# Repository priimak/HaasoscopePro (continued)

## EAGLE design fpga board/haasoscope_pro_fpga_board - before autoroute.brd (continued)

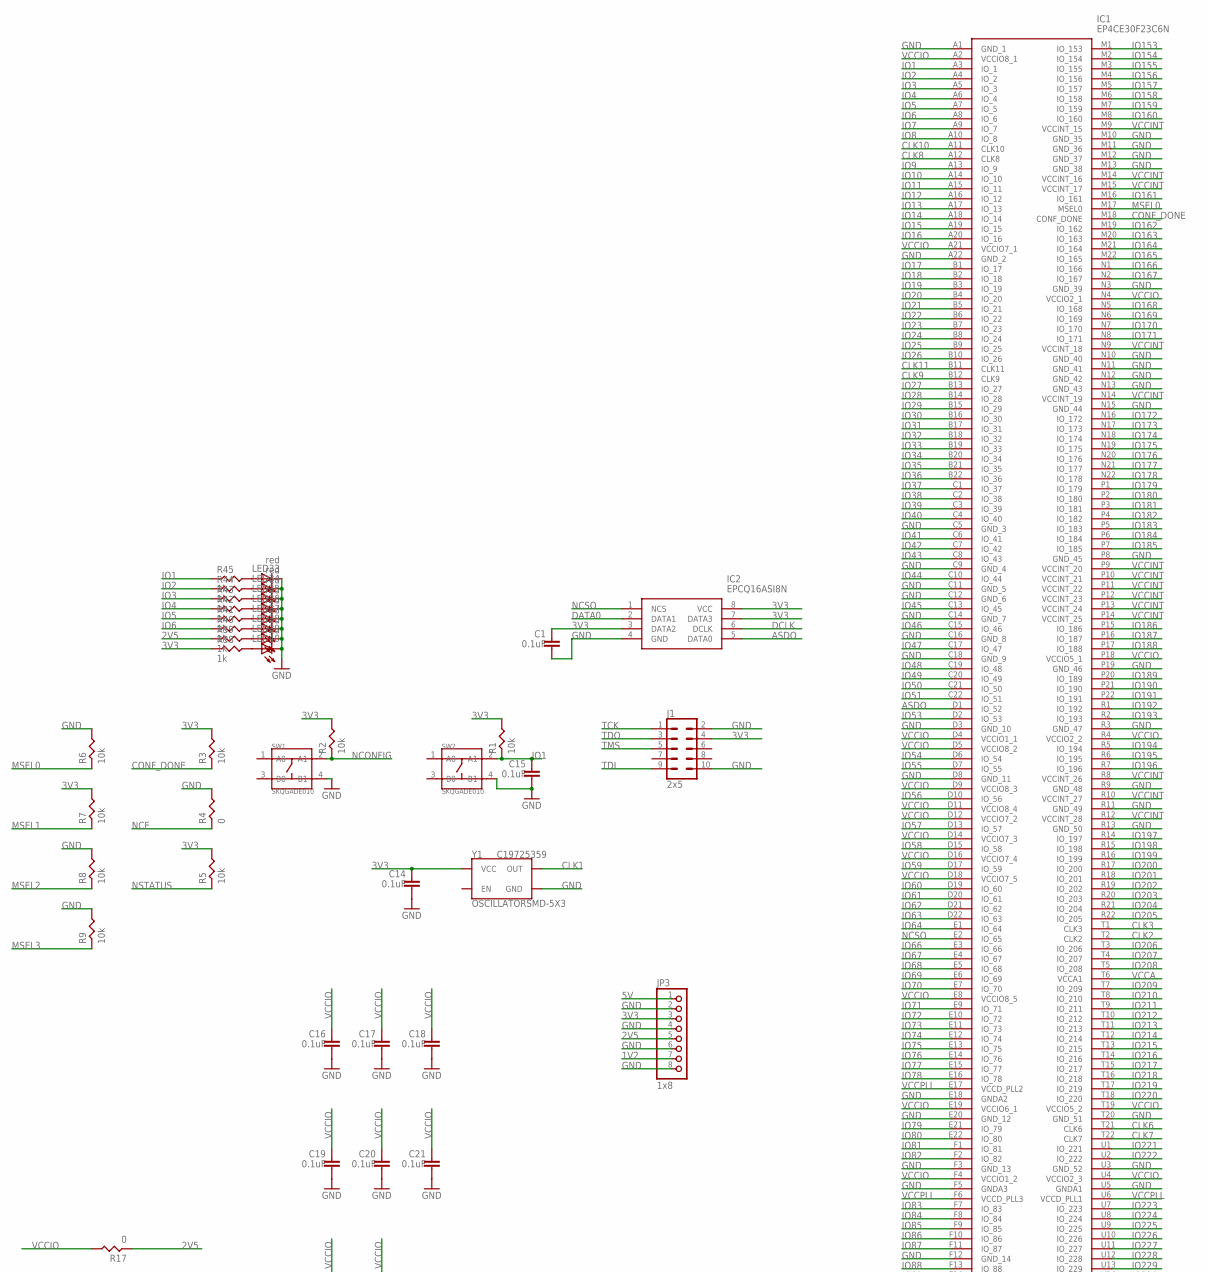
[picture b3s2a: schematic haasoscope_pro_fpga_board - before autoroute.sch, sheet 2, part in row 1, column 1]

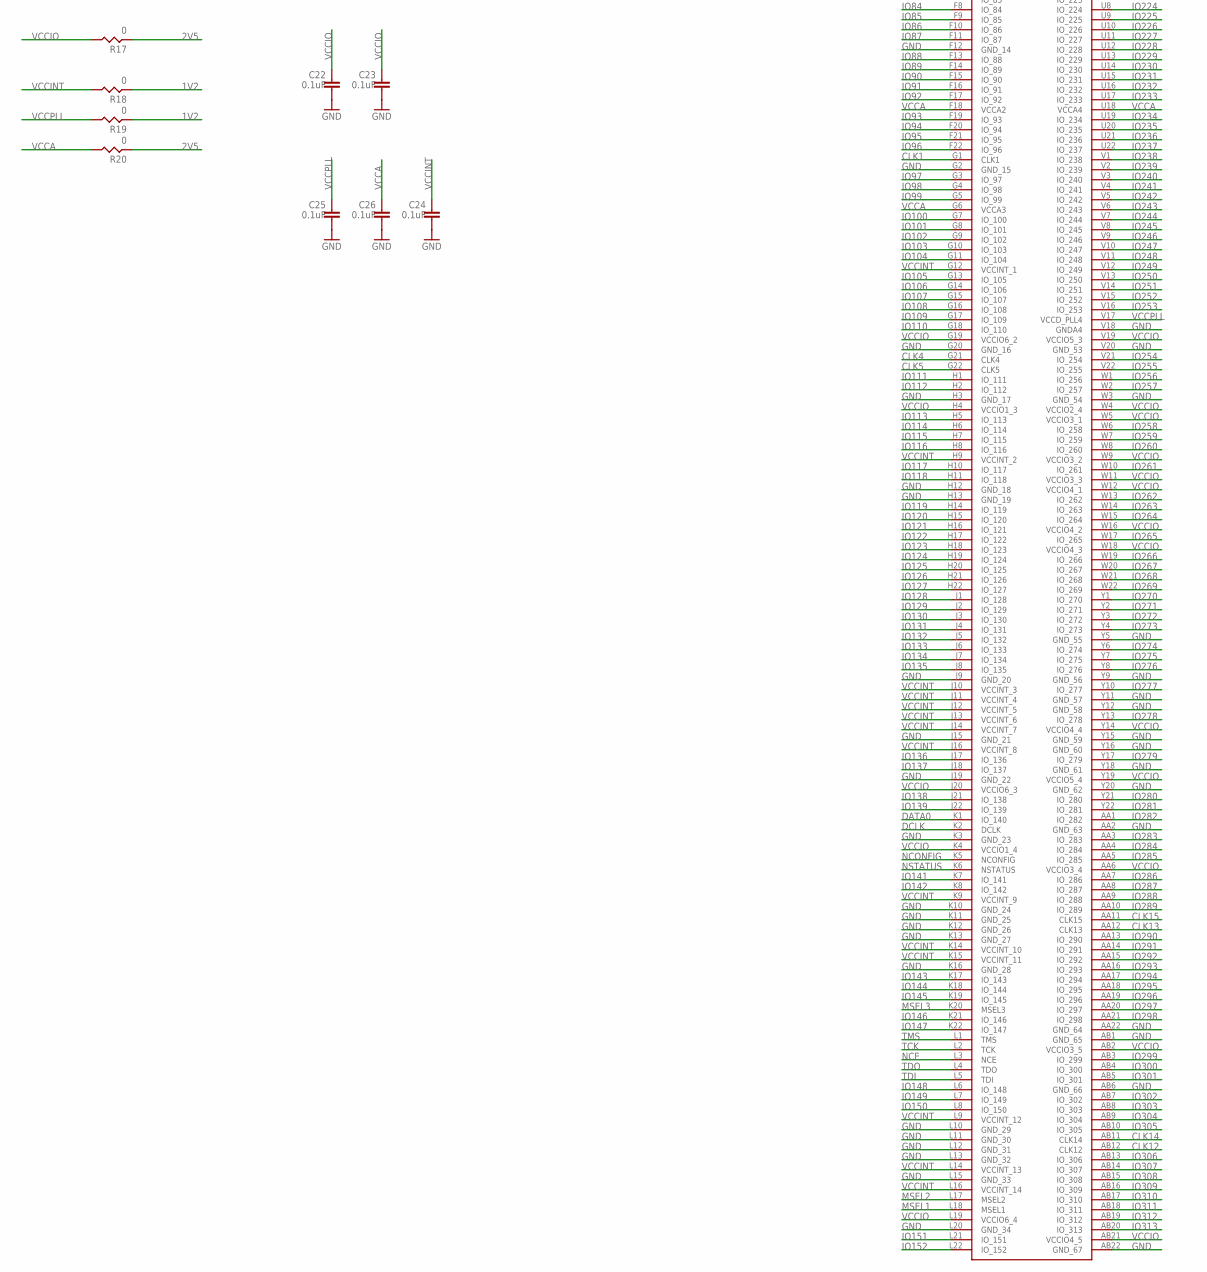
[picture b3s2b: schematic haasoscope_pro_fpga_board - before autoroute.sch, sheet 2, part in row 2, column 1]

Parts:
C1, C14, C15, C16, C17, C18, C19, C20, C21, C22, C23, C24, C25, C26: 0.1uF; RESC0402_N
IC1: EP4CE30F23C6N; BGA484C100P22X22_2300X2300X240
IC2: EPCQ16ASI8N; SOIC127P600X175-8N
J1: 2x5; 2X5-SHROUDED
JP3: 1x8; 1X08
LED33, LED34, LED35, LED36, LED37, LED38, LED39, LED40: red; CHIP-LED0603
R1, R2, R3, R5, R6, R7, R8, R9: 10k; RES-0402
R4, R17, R18, R19, R20: 0; RES-0402
R38, R39, R40, R41, R42, R43, R44, R45: 1k; RES-0402
SW1, SW2: SKQGADE010; SW4-SMD-5.2X5.2X1.5MM
Y1: OSCILLATORSMD-5X3; OSCILLATOR-SMD-5X3.2; LCSC C19725359

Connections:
1V2: JP3.7, R18.P$1, R19.P$1; also elsewhere on the board
2V5: JP3.5, R17.P$1, R20.P$1, R39.P$1; also elsewhere on the board
3V3: C1.2, C14.2, IC2.3 (DATA2), IC2.7 (DATA3), IC2.8 (VCC), J1.4, JP3.3, R1.P$2, R2.P$2, R3.P$2, R5.P$2, R7.P$2, R38.P$1, Y1.4 (VCC); also elsewhere on the board
5V: JP3.1; also elsewhere on the board
ASDO: IC1.D1 (IO_52), IC2.5 (DATA0); also elsewhere on the board
CLK1: IC1.G1 (CLK1), Y1.3 (OUT); also elsewhere on the board
CLK2: IC1.T2 (CLK2); also elsewhere on the board
CLK3: IC1.T1 (CLK3); also elsewhere on the board
CLK4: IC1.G21 (CLK4); also elsewhere on the board
CLK5: IC1.G22 (CLK5); also elsewhere on the board
CLK6: IC1.T21 (CLK6); also elsewhere on the board
CLK7: IC1.T22 (CLK7); also elsewhere on the board
CLK8: IC1.A12 (CLK8); also elsewhere on the board
CLK9: IC1.B12 (CLK9); also elsewhere on the board
CLK10: IC1.A11 (CLK10); also elsewhere on the board
CLK11: IC1.B11 (CLK11); also elsewhere on the board
CLK12: IC1.AB12 (CLK12); also elsewhere on the board
CLK13: IC1.AA12 (CLK13); also elsewhere on the board
CLK14: IC1.AB11 (CLK14); also elsewhere on the board
CLK15: IC1.AA11 (CLK15); also elsewhere on the board
CONF_DONE: IC1.M18 (CONF_DONE), R3.P$1
DATA0: IC1.K1 (IO_140), IC2.2 (DATA1); also elsewhere on the board
DCLK: IC1.K2 (DCLK), IC2.6 (DCLK)
GND: C1.1, C14.1, C15.1, C16.1, C17.1, C18.1, C19.1, C20.1, C21.1, C22.1, C23.1, C24.1, C25.1, C26.1, IC1.A1 (GND_1), IC1.A22 (GND_2), IC1.AA2 (GND_63), IC1.AA22 (GND_64), IC1.AB1 (GND_65), IC1.AB6 (GND_66), IC1.AB22 (GND_67), IC1.C5 (GND_3), IC1.C9 (GND_4), IC1.C11 (GND_5), IC1.C12 (GND_6), IC1.C14 (GND_7), IC1.C16 (GND_8), IC1.C18 (GND_9), IC1.D3 (GND_10), IC1.D8 (GND_11), IC1.E18 (GNDA2), IC1.E20 (GND_12), IC1.F3 (GND_13), IC1.F5 (GNDA3), IC1.F12 (GND_14), IC1.G2 (GND_15), IC1.G20 (GND_16), IC1.H3 (GND_17), IC1.H12 (GND_18), IC1.H13 (GND_19), IC1.J9 (GND_20), IC1.J15 (GND_21), IC1.J19 (GND_22), IC1.K3 (GND_23), IC1.K10 (GND_24), IC1.K11 (GND_25), IC1.K12 (GND_26), IC1.K13 (GND_27), IC1.K16 (GND_28), IC1.L10 (GND_29), IC1.L11 (GND_30), IC1.L12 (GND_31), IC1.L13 (GND_32), IC1.L15 (GND_33), IC1.L20 (GND_34), IC1.M10 (GND_35), IC1.M11 (GND_36), IC1.M12 (GND_37), IC1.M13 (GND_38), IC1.N3 (GND_39), IC1.N10 (GND_40), IC1.N11 (GND_41), IC1.N12 (GND_42), IC1.N13 (GND_43), IC1.N15 (GND_44), IC1.P8 (GND_45), IC1.P19 (GND_46), IC1.R3 (GND_47), IC1.R9 (GND_48), IC1.R11 (GND_49), IC1.R13 (GND_50), IC1.T20 (GND_51), IC1.U3 (GND_52), IC1.U5 (GNDA1), IC1.V18 (GNDA4), IC1.V20 (GND_53), IC1.W3 (GND_54), IC1.Y5 (GND_55), IC1.Y9 (GND_56), IC1.Y11 (GND_57), IC1.Y12 (GND_58), IC1.Y15 (GND_59), IC1.Y16 (GND_60), IC1.Y18 (GND_61), IC1.Y20 (GND_62), IC2.4 (GND), J1.2, J1.10, JP3.2, JP3.4, JP3.6, JP3.8, LED33.C, LED34.C, LED35.C, LED36.C, LED37.C, LED38.C, LED39.C, LED40.C, R4.P$2, R6.P$2, R8.P$2, R9.P$2, SW1.4 (B1), SW2.4 (B1), Y1.2 (GND); also elsewhere on the board
IO1: C15.2, IC1.A3 (IO_1), R1.P$1, R45.P$1, SW2.2 (A1); also elsewhere on the board
IO2: IC1.A4 (IO_2), R44.P$1; also elsewhere on the board
IO3: IC1.A5 (IO_3), R43.P$1; also elsewhere on the board
IO4: IC1.A6 (IO_4), R42.P$1; also elsewhere on the board
IO5: IC1.A7 (IO_5), R41.P$1; also elsewhere on the board
IO6: IC1.A8 (IO_6), R40.P$1; also elsewhere on the board
IO7: IC1.A9 (IO_7); also elsewhere on the board
IO8: IC1.A10 (IO_8); also elsewhere on the board
IO9: IC1.A13 (IO_9); also elsewhere on the board
IO10: IC1.A14 (IO_10); also elsewhere on the board
IO11: IC1.A15 (IO_11); also elsewhere on the board
IO12: IC1.A16 (IO_12); also elsewhere on the board
IO13: IC1.A17 (IO_13); also elsewhere on the board
IO14: IC1.A18 (IO_14); also elsewhere on the board
IO15: IC1.A19 (IO_15); also elsewhere on the board
IO16: IC1.A20 (IO_16); also elsewhere on the board
IO17: IC1.B1 (IO_17); also elsewhere on the board
IO18: IC1.B2 (IO_18); also elsewhere on the board
IO19: IC1.B3 (IO_19); also elsewhere on the board
IO20: IC1.B4 (IO_20); also elsewhere on the board
IO21: IC1.B5 (IO_21); also elsewhere on the board
IO22: IC1.B6 (IO_22); also elsewhere on the board
IO23: IC1.B7 (IO_23); also elsewhere on the board
IO24: IC1.B8 (IO_24); also elsewhere on the board
IO25: IC1.B9 (IO_25); also elsewhere on the board
IO26: IC1.B10 (IO_26); also elsewhere on the board
IO27: IC1.B13 (IO_27); also elsewhere on the board
IO28: IC1.B14 (IO_28); also elsewhere on the board
IO29: IC1.B15 (IO_29); also elsewhere on the board
IO30: IC1.B16 (IO_30); also elsewhere on the board
IO31: IC1.B17 (IO_31); also elsewhere on the board
IO32: IC1.B18 (IO_32); also elsewhere on the board
IO33: IC1.B19 (IO_33); also elsewhere on the board
IO34: IC1.B20 (IO_34); also elsewhere on the board
IO35: IC1.B21 (IO_35); also elsewhere on the board
IO36: IC1.B22 (IO_36); also elsewhere on the board
IO37: IC1.C1 (IO_37); also elsewhere on the board
IO38: IC1.C2 (IO_38); also elsewhere on the board
IO39: IC1.C3 (IO_39); also elsewhere on the board
IO40: IC1.C4 (IO_40); also elsewhere on the board
IO41: IC1.C6 (IO_41); also elsewhere on the board
IO42: IC1.C7 (IO_42); also elsewhere on the board
IO43: IC1.C8 (IO_43); also elsewhere on the board
IO44: IC1.C10 (IO_44); also elsewhere on the board
IO45: IC1.C13 (IO_45); also elsewhere on the board
IO46: IC1.C15 (IO_46); also elsewhere on the board
IO47: IC1.C17 (IO_47); also elsewhere on the board
IO48: IC1.C19 (IO_48); also elsewhere on the board
IO49: IC1.C20 (IO_49); also elsewhere on the board
IO50: IC1.C21 (IO_50); also elsewhere on the board
IO51: IC1.C22 (IO_51); also elsewhere on the board
IO53: IC1.D2 (IO_53); also elsewhere on the board
IO54: IC1.D6 (IO_54); also elsewhere on the board
IO55: IC1.D7 (IO_55); also elsewhere on the board
IO56: IC1.D10 (IO_56); also elsewhere on the board
IO57: IC1.D13 (IO_57); also elsewhere on the board
IO58: IC1.D15 (IO_58); also elsewhere on the board
IO59: IC1.D17 (IO_59); also elsewhere on the board
IO60: IC1.D19 (IO_60); also elsewhere on the board
IO61: IC1.D20 (IO_61); also elsewhere on the board
IO62: IC1.D21 (IO_62); also elsewhere on the board
IO63: IC1.D22 (IO_63); also elsewhere on the board
IO64: IC1.E1 (IO_64); also elsewhere on the board
IO66: IC1.E3 (IO_66); also elsewhere on the board
IO67: IC1.E4 (IO_67); also elsewhere on the board
IO68: IC1.E5 (IO_68); also elsewhere on the board
IO69: IC1.E6 (IO_69); also elsewhere on the board
IO70: IC1.E7 (IO_70); also elsewhere on the board
IO71: IC1.E9 (IO_71); also elsewhere on the board
IO72: IC1.E10 (IO_72); also elsewhere on the board
IO73: IC1.E11 (IO_73); also elsewhere on the board
IO74: IC1.E12 (IO_74); also elsewhere on the board
IO75: IC1.E13 (IO_75); also elsewhere on the board
IO76: IC1.E14 (IO_76); also elsewhere on the board
IO77: IC1.E15 (IO_77); also elsewhere on the board
IO78: IC1.E16 (IO_78); also elsewhere on the board
IO79: IC1.E21 (IO_79); also elsewhere on the board
IO80: IC1.E22 (IO_80); also elsewhere on the board
IO81: IC1.F1 (IO_81); also elsewhere on the board
IO82: IC1.F2 (IO_82); also elsewhere on the board
IO83: IC1.F7 (IO_83); also elsewhere on the board
IO84: IC1.F8 (IO_84); also elsewhere on the board
IO85: IC1.F9 (IO_85); also elsewhere on the board
IO86: IC1.F10 (IO_86); also elsewhere on the board
IO87: IC1.F11 (IO_87); also elsewhere on the board
IO88: IC1.F13 (IO_88); also elsewhere on the board
IO89: IC1.F14 (IO_89); also elsewhere on the board
IO90: IC1.F15 (IO_90); also elsewhere on the board
IO91: IC1.F16 (IO_91); also elsewhere on the board
IO92: IC1.F17 (IO_92); also elsewhere on the board
IO93: IC1.F19 (IO_93); also elsewhere on the board
IO94: IC1.F20 (IO_94); also elsewhere on the board
IO95: IC1.F21 (IO_95); also elsewhere on the board
IO96: IC1.F22 (IO_96); also elsewhere on the board
IO97: IC1.G3 (IO_97); also elsewhere on the board
IO98: IC1.G4 (IO_98); also elsewhere on the board
IO99: IC1.G5 (IO_99); also elsewhere on the board
IO100: IC1.G7 (IO_100); also elsewhere on the board
IO101: IC1.G8 (IO_101); also elsewhere on the board
IO102: IC1.G9 (IO_102); also elsewhere on the board
IO103: IC1.G10 (IO_103); also elsewhere on the board
IO104: IC1.G11 (IO_104); also elsewhere on the board
IO105: IC1.G13 (IO_105); also elsewhere on the board
IO106: IC1.G14 (IO_106); also elsewhere on the board
IO107: IC1.G15 (IO_107); also elsewhere on the board
IO108: IC1.G16 (IO_108); also elsewhere on the board
IO109: IC1.G17 (IO_109); also elsewhere on the board
IO110: IC1.G18 (IO_110); also elsewhere on the board
IO111: IC1.H1 (IO_111); also elsewhere on the board
IO112: IC1.H2 (IO_112); also elsewhere on the board
IO113: IC1.H5 (IO_113); also elsewhere on the board
IO114: IC1.H6 (IO_114); also elsewhere on the board
IO115: IC1.H7 (IO_115); also elsewhere on the board
IO116: IC1.H8 (IO_116); also elsewhere on the board
IO117: IC1.H10 (IO_117); also elsewhere on the board
IO118: IC1.H11 (IO_118); also elsewhere on the board
IO119: IC1.H14 (IO_119); also elsewhere on the board
IO120: IC1.H15 (IO_120); also elsewhere on the board
IO121: IC1.H16 (IO_121); also elsewhere on the board
IO122: IC1.H17 (IO_122); also elsewhere on the board
IO123: IC1.H18 (IO_123); also elsewhere on the board
IO124: IC1.H19 (IO_124); also elsewhere on the board
IO125: IC1.H20 (IO_125); also elsewhere on the board
IO126: IC1.H21 (IO_126); also elsewhere on the board
IO127: IC1.H22 (IO_127); also elsewhere on the board
IO128: IC1.J1 (IO_128); also elsewhere on the board
IO129: IC1.J2 (IO_129); also elsewhere on the board
IO130: IC1.J3 (IO_130); also elsewhere on the board
IO131: IC1.J4 (IO_131); also elsewhere on the board
IO132: IC1.J5 (IO_132); also elsewhere on the board
IO133: IC1.J6 (IO_133); also elsewhere on the board
IO134: IC1.J7 (IO_134); also elsewhere on the board
IO135: IC1.J8 (IO_135); also elsewhere on the board
IO136: IC1.J17 (IO_136); also elsewhere on the board
IO137: IC1.J18 (IO_137); also elsewhere on the board
IO138: IC1.J21 (IO_138); also elsewhere on the board
IO139: IC1.J22 (IO_139); also elsewhere on the board
IO141: IC1.K7 (IO_141); also elsewhere on the board
IO142: IC1.K8 (IO_142); also elsewhere on the board
IO143: IC1.K17 (IO_143); also elsewhere on the board
IO144: IC1.K18 (IO_144); also elsewhere on the board
IO145: IC1.K19 (IO_145); also elsewhere on the board
IO146: IC1.K21 (IO_146); also elsewhere on the board
IO147: IC1.K22 (IO_147); also elsewhere on the board
IO148: IC1.L6 (IO_148); also elsewhere on the board
IO149: IC1.L7 (IO_149); also elsewhere on the board
IO150: IC1.L8 (IO_150); also elsewhere on the board
IO151: IC1.L21 (IO_151); also elsewhere on the board
IO152: IC1.L22 (IO_152); also elsewhere on the board
IO153: IC1.M1 (IO_153); also elsewhere on the board
IO154: IC1.M2 (IO_154); also elsewhere on the board
IO155: IC1.M3 (IO_155); also elsewhere on the board
IO156: IC1.M4 (IO_156); also elsewhere on the board
IO157: IC1.M5 (IO_157); also elsewhere on the board
IO158: IC1.M6 (IO_158); also elsewhere on the board
IO159: IC1.M7 (IO_159); also elsewhere on the board
IO160: IC1.M8 (IO_160); also elsewhere on the board
IO161: IC1.M16 (IO_161); also elsewhere on the board
IO162: IC1.M19 (IO_162); also elsewhere on the board
IO163: IC1.M20 (IO_163); also elsewhere on the board
IO164: IC1.M21 (IO_164); also elsewhere on the board
IO165: IC1.M22 (IO_165); also elsewhere on the board
IO166: IC1.N1 (IO_166); also elsewhere on the board
IO167: IC1.N2 (IO_167); also elsewhere on the board
IO168: IC1.N5 (IO_168); also elsewhere on the board
IO169: IC1.N6 (IO_169); also elsewhere on the board
IO170: IC1.N7 (IO_170); also elsewhere on the board
IO171: IC1.N8 (IO_171); also elsewhere on the board
IO172: IC1.N16 (IO_172); also elsewhere on the board
IO173: IC1.N17 (IO_173); also elsewhere on the board
IO174: IC1.N18 (IO_174); also elsewhere on the board
IO175: IC1.N19 (IO_175); also elsewhere on the board
IO176: IC1.N20 (IO_176); also elsewhere on the board
IO177: IC1.N21 (IO_177); also elsewhere on the board
IO178: IC1.N22 (IO_178); also elsewhere on the board
IO179: IC1.P1 (IO_179); also elsewhere on the board
IO180: IC1.P2 (IO_180); also elsewhere on the board
IO181: IC1.P3 (IO_181); also elsewhere on the board
IO182: IC1.P4 (IO_182); also elsewhere on the board
IO183: IC1.P5 (IO_183); also elsewhere on the board
IO184: IC1.P6 (IO_184); also elsewhere on the board
IO185: IC1.P7 (IO_185); also elsewhere on the board
IO186: IC1.P15 (IO_186); also elsewhere on the board
IO187: IC1.P16 (IO_187); also elsewhere on the board
IO188: IC1.P17 (IO_188); also elsewhere on the board
IO189: IC1.P20 (IO_189); also elsewhere on the board
IO190: IC1.P21 (IO_190); also elsewhere on the board
IO191: IC1.P22 (IO_191); also elsewhere on the board
IO192: IC1.R1 (IO_192); also elsewhere on the board
IO193: IC1.R2 (IO_193); also elsewhere on the board
IO194: IC1.R5 (IO_194); also elsewhere on the board
IO195: IC1.R6 (IO_195); also elsewhere on the board
IO196: IC1.R7 (IO_196); also elsewhere on the board
IO197: IC1.R14 (IO_197); also elsewhere on the board
IO198: IC1.R15 (IO_198); also elsewhere on the board
IO199: IC1.R16 (IO_199); also elsewhere on the board
IO200: IC1.R17 (IO_200); also elsewhere on the board
IO201: IC1.R18 (IO_201); also elsewhere on the board
IO202: IC1.R19 (IO_202); also elsewhere on the board
IO203: IC1.R20 (IO_203); also elsewhere on the board
IO204: IC1.R21 (IO_204); also elsewhere on the board
IO205: IC1.R22 (IO_205); also elsewhere on the board
IO206: IC1.T3 (IO_206); also elsewhere on the board
IO207: IC1.T4 (IO_207); also elsewhere on the board
IO208: IC1.T5 (IO_208); also elsewhere on the board
IO209: IC1.T7 (IO_209); also elsewhere on the board
IO210: IC1.T8 (IO_210); also elsewhere on the board
IO211: IC1.T9 (IO_211); also elsewhere on the board
IO212: IC1.T10 (IO_212); also elsewhere on the board
IO213: IC1.T11 (IO_213); also elsewhere on the board
IO214: IC1.T12 (IO_214); also elsewhere on the board
IO215: IC1.T13 (IO_215); also elsewhere on the board
IO216: IC1.T14 (IO_216); also elsewhere on the board
IO217: IC1.T15 (IO_217); also elsewhere on the board
IO218: IC1.T16 (IO_218); also elsewhere on the board
IO219: IC1.T17 (IO_219); also elsewhere on the board
IO220: IC1.T18 (IO_220); also elsewhere on the board
IO221: IC1.U1 (IO_221); also elsewhere on the board
IO222: IC1.U2 (IO_222); also elsewhere on the board
IO223: IC1.U7 (IO_223); also elsewhere on the board
IO224: IC1.U8 (IO_224); also elsewhere on the board
IO225: IC1.U9 (IO_225); also elsewhere on the board
IO226: IC1.U10 (IO_226); also elsewhere on the board
IO227: IC1.U11 (IO_227); also elsewhere on the board
IO228: IC1.U12 (IO_228); also elsewhere on the board
IO229: IC1.U13 (IO_229); also elsewhere on the board
IO230: IC1.U14 (IO_230); also elsewhere on the board
IO231: IC1.U15 (IO_231); also elsewhere on the board
IO232: IC1.U16 (IO_232); also elsewhere on the board
IO233: IC1.U17 (IO_233); also elsewhere on the board
IO234: IC1.U19 (IO_234); also elsewhere on the board
IO235: IC1.U20 (IO_235); also elsewhere on the board
IO236: IC1.U21 (IO_236); also elsewhere on the board
IO237: IC1.U22 (IO_237); also elsewhere on the board
IO238: IC1.V1 (IO_238); also elsewhere on the board
IO239: IC1.V2 (IO_239); also elsewhere on the board
IO240: IC1.V3 (IO_240); also elsewhere on the board
IO241: IC1.V4 (IO_241); also elsewhere on the board
IO242: IC1.V5 (IO_242); also elsewhere on the board
IO243: IC1.V6 (IO_243); also elsewhere on the board
IO244: IC1.V7 (IO_244); also elsewhere on the board
IO245: IC1.V8 (IO_245); also elsewhere on the board
IO246: IC1.V9 (IO_246); also elsewhere on the board
IO247: IC1.V10 (IO_247); also elsewhere on the board
IO248: IC1.V11 (IO_248); also elsewhere on the board
IO249: IC1.V12 (IO_249); also elsewhere on the board
IO250: IC1.V13 (IO_250); also elsewhere on the board
IO251: IC1.V14 (IO_251); also elsewhere on the board
IO252: IC1.V15 (IO_252); also elsewhere on the board
IO253: IC1.V16 (IO_253); also elsewhere on the board
IO254: IC1.V21 (IO_254); also elsewhere on the board
IO255: IC1.V22 (IO_255); also elsewhere on the board
IO256: IC1.W1 (IO_256); also elsewhere on the board
IO257: IC1.W2 (IO_257); also elsewhere on the board
IO258: IC1.W6 (IO_258); also elsewhere on the board
IO259: IC1.W7 (IO_259); also elsewhere on the board
IO260: IC1.W8 (IO_260); also elsewhere on the board
IO261: IC1.W10 (IO_261); also elsewhere on the board
IO262: IC1.W13 (IO_262); also elsewhere on the board
IO263: IC1.W14 (IO_263); also elsewhere on the board
IO264: IC1.W15 (IO_264); also elsewhere on the board
IO265: IC1.W17 (IO_265); also elsewhere on the board
IO266: IC1.W19 (IO_266); also elsewhere on the board
IO267: IC1.W20 (IO_267); also elsewhere on the board
IO268: IC1.W21 (IO_268); also elsewhere on the board
IO269: IC1.W22 (IO_269); also elsewhere on the board
IO270: IC1.Y1 (IO_270); also elsewhere on the board
IO271: IC1.Y2 (IO_271); also elsewhere on the board
IO272: IC1.Y3 (IO_272); also elsewhere on the board
IO273: IC1.Y4 (IO_273); also elsewhere on the board
IO274: IC1.Y6 (IO_274); also elsewhere on the board
IO275: IC1.Y7 (IO_275); also elsewhere on the board
IO276: IC1.Y8 (IO_276); also elsewhere on the board
IO277: IC1.Y10 (IO_277); also elsewhere on the board
IO278: IC1.Y13 (IO_278); also elsewhere on the board
IO279: IC1.Y17 (IO_279); also elsewhere on the board
IO280: IC1.Y21 (IO_280); also elsewhere on the board
IO281: IC1.Y22 (IO_281); also elsewhere on the board
IO282: IC1.AA1 (IO_282); also elsewhere on the board
IO283: IC1.AA3 (IO_283); also elsewhere on the board
IO284: IC1.AA4 (IO_284); also elsewhere on the board
IO285: IC1.AA5 (IO_285); also elsewhere on the board
IO286: IC1.AA7 (IO_286); also elsewhere on the board
IO287: IC1.AA8 (IO_287); also elsewhere on the board
IO288: IC1.AA9 (IO_288); also elsewhere on the board
IO289: IC1.AA10 (IO_289); also elsewhere on the board
IO290: IC1.AA13 (IO_290); also elsewhere on the board
IO291: IC1.AA14 (IO_291); also elsewhere on the board
IO292: IC1.AA15 (IO_292); also elsewhere on the board
IO293: IC1.AA16 (IO_293); also elsewhere on the board
IO294: IC1.AA17 (IO_294); also elsewhere on the board
IO295: IC1.AA18 (IO_295); also elsewhere on the board
IO296: IC1.AA19 (IO_296); also elsewhere on the board
IO297: IC1.AA20 (IO_297); also elsewhere on the board
IO298: IC1.AA21 (IO_298); also elsewhere on the board
IO299: IC1.AB3 (IO_299); also elsewhere on the board
IO300: IC1.AB4 (IO_300); also elsewhere on the board
IO301: IC1.AB5 (IO_301); also elsewhere on the board
IO302: IC1.AB7 (IO_302); also elsewhere on the board
IO303: IC1.AB8 (IO_303); also elsewhere on the board
IO304: IC1.AB9 (IO_304); also elsewhere on the board
IO305: IC1.AB10 (IO_305); also elsewhere on the board
IO306: IC1.AB13 (IO_306); also elsewhere on the board
IO307: IC1.AB14 (IO_307); also elsewhere on the board
IO308: IC1.AB15 (IO_308); also elsewhere on the board
IO309: IC1.AB16 (IO_309); also elsewhere on the board
IO310: IC1.AB17 (IO_310); also elsewhere on the board
IO311: IC1.AB18 (IO_311); also elsewhere on the board
IO312: IC1.AB19 (IO_312); also elsewhere on the board
IO313: IC1.AB20 (IO_313); also elsewhere on the board
MSEL0: IC1.M17 (MSEL0), R6.P$1
MSEL1: IC1.L18 (MSEL1), R7.P$1
MSEL2: IC1.L17 (MSEL2), R8.P$1
MSEL3: IC1.K20 (MSEL3), R9.P$1
unnamed: LED33.A, R45.P$2
unnamed: LED34.A, R44.P$2
unnamed: LED35.A, R43.P$2
unnamed: LED36.A, R42.P$2
unnamed: LED37.A, R41.P$2
unnamed: LED38.A, R40.P$2
unnamed: LED39.A, R39.P$2
unnamed: LED40.A, R38.P$2
NCE: IC1.L3 (NCE), R4.P$1
NCONFIG: IC1.K5 (NCONFIG), R2.P$1, SW1.2 (A1)
NCSO: IC1.E2 (IO_65), IC2.1 (NCS); also elsewhere on the board
NSTATUS: IC1.K6 (NSTATUS), R5.P$1
TCK: IC1.L2 (TCK), J1.1
TDI: IC1.L5 (TDI), J1.9
TDO: IC1.L4 (TDO), J1.3
TMS: IC1.L1 (TMS), J1.5
VCCA: C26.2, IC1.F18 (VCCA2), IC1.G6 (VCCA3), IC1.T6 (VCCA1), IC1.U18 (VCCA4), R20.P$2
VCCINT: C24.2, IC1.G12 (VCCINT_1), IC1.H9 (VCCINT_2), IC1.J10 (VCCINT_3), IC1.J11 (VCCINT_4), IC1.J12 (VCCINT_5), IC1.J13 (VCCINT_6), IC1.J14 (VCCINT_7), IC1.J16 (VCCINT_8), IC1.K9 (VCCINT_9), IC1.K14 (VCCINT_10), IC1.K15 (VCCINT_11), IC1.L9 (VCCINT_12), IC1.L14 (VCCINT_13), IC1.L16 (VCCINT_14), IC1.M9 (VCCINT_15), IC1.M14 (VCCINT_16), IC1.M15 (VCCINT_17), IC1.N9 (VCCINT_18), IC1.N14 (VCCINT_19), IC1.P9 (VCCINT_20), IC1.P10 (VCCINT_21), IC1.P11 (VCCINT_22), IC1.P12 (VCCINT_23), IC1.P13 (VCCINT_24), IC1.P14 (VCCINT_25), IC1.R8 (VCCINT_26), IC1.R10 (VCCINT_27), IC1.R12 (VCCINT_28), R18.P$2
VCCIO: C16.2, C17.2, C18.2, C19.2, C20.2, C21.2, C22.2, C23.2, IC1.A2 (VCCIO8_1), IC1.A21 (VCCIO7_1), IC1.AA6 (VCCIO3_4), IC1.AB2 (VCCIO3_5), IC1.AB21 (VCCIO4_5), IC1.D4 (VCCIO1_1), IC1.D5 (VCCIO8_2), IC1.D9 (VCCIO8_3), IC1.D11 (VCCIO8_4), IC1.D12 (VCCIO7_2), IC1.D14 (VCCIO7_3), IC1.D16 (VCCIO7_4), IC1.D18 (VCCIO7_5), IC1.E8 (VCCIO8_5), IC1.E19 (VCCIO6_1), IC1.F4 (VCCIO1_2), IC1.G19 (VCCIO6_2), IC1.H4 (VCCIO1_3), IC1.J20 (VCCIO6_3), IC1.K4 (VCCIO1_4), IC1.L19 (VCCIO6_4), IC1.N4 (VCCIO2_1), IC1.P18 (VCCIO5_1), IC1.R4 (VCCIO2_2), IC1.T19 (VCCIO5_2), IC1.U4 (VCCIO2_3), IC1.V19 (VCCIO5_3), IC1.W4 (VCCIO2_4), IC1.W5 (VCCIO3_1), IC1.W9 (VCCIO3_2), IC1.W11 (VCCIO3_3), IC1.W12 (VCCIO4_1), IC1.W16 (VCCIO4_2), IC1.W18 (VCCIO4_3), IC1.Y14 (VCCIO4_4), IC1.Y19 (VCCIO5_4), R17.P$2
VCCPLL: C25.2, IC1.E17 (VCCD_PLL2), IC1.F6 (VCCD_PLL3), IC1.U6 (VCCD_PLL1), IC1.V17 (VCCD_PLL4), R19.P$2

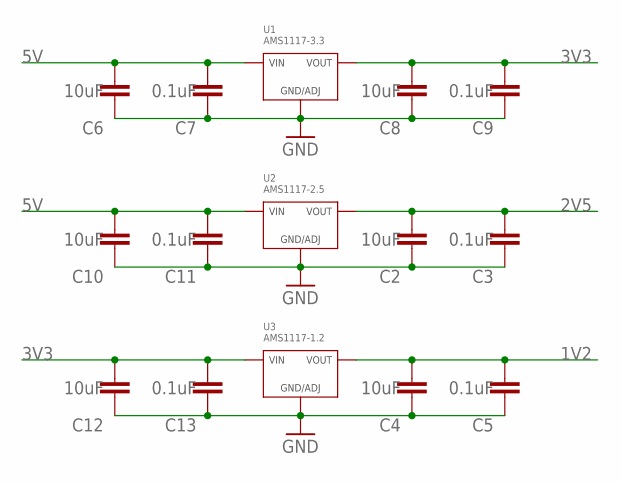
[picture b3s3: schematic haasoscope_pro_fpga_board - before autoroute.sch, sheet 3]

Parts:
C2, C4, C6, C8, C10, C12: 10uF; RESC0805_N
C3, C5, C7, C9, C11, C13: 0.1uF; RESC0402_N
U1: AMS1117-3.3; SOT-223-3; MPN AMS1117-3.3
U2: AMS1117-2.5; SOT-223-3; MPN AMS1117-2.5
U3: AMS1117-1.2; SOT-223-3; MPN AMS1117-1.2

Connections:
1V2: C4.2, C5.2, U3.P$1 (VOUT), U3.P$3 (VOUT); also elsewhere on the board
2V5: C2.2, C3.2, U2.P$1 (VOUT), U2.P$3 (VOUT); also elsewhere on the board
3V3: C8.2, C9.2, C12.2, C13.2, U1.P$1 (VOUT), U1.P$3 (VOUT), U3.P$4 (VIN); also elsewhere on the board
5V: C6.2, C7.2, C10.2, C11.2, U1.P$4 (VIN), U2.P$4 (VIN); also elsewhere on the board
GND: C2.1, C3.1, C4.1, C5.1, C6.1, C7.1, C8.1, C9.1, C10.1, C11.1, C12.1, C13.1, U1.P$2 (GND/ADJ), U2.P$2 (GND/ADJ), U3.P$2 (GND/ADJ); also elsewhere on the board

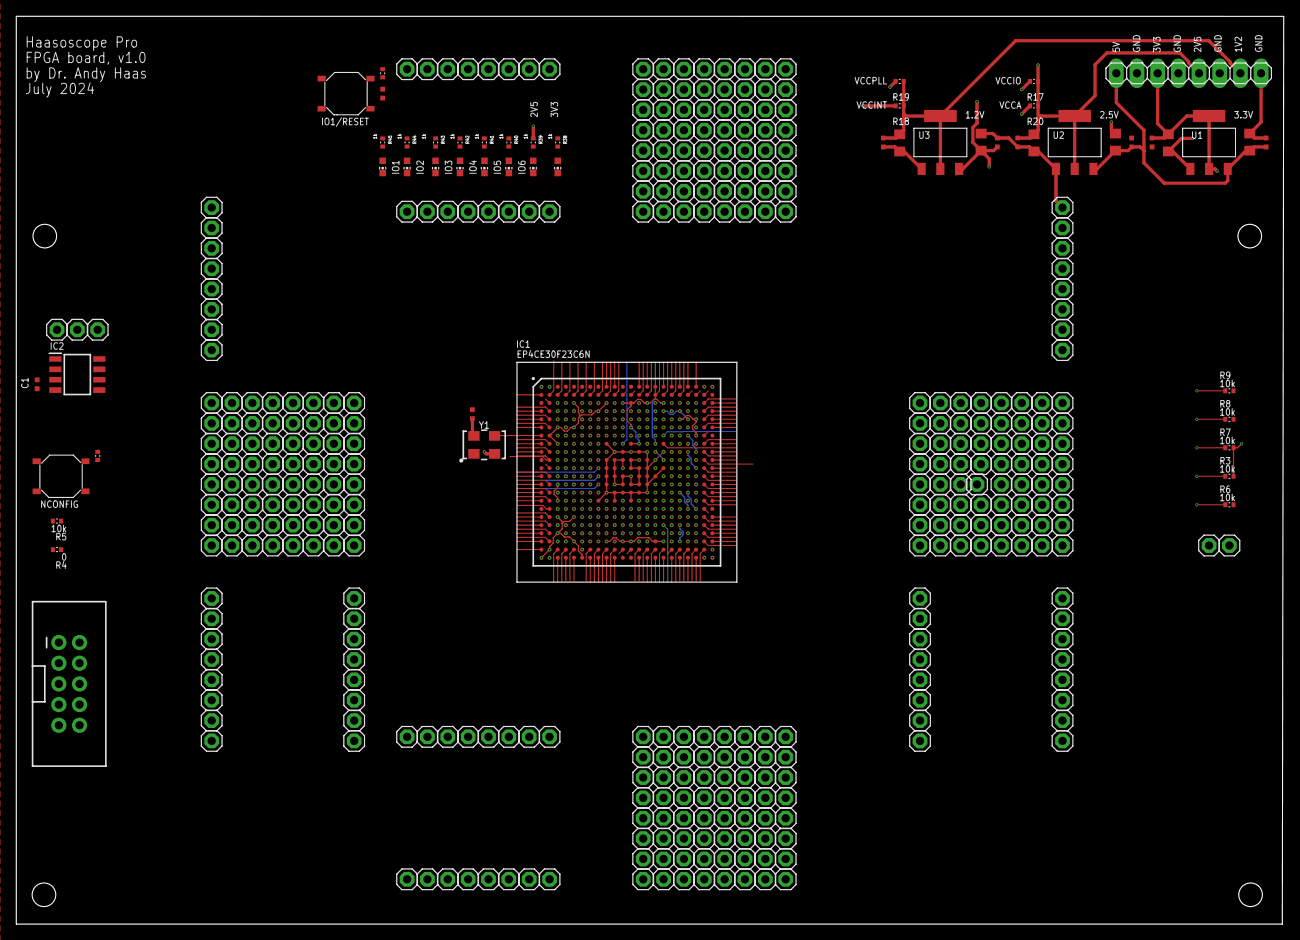
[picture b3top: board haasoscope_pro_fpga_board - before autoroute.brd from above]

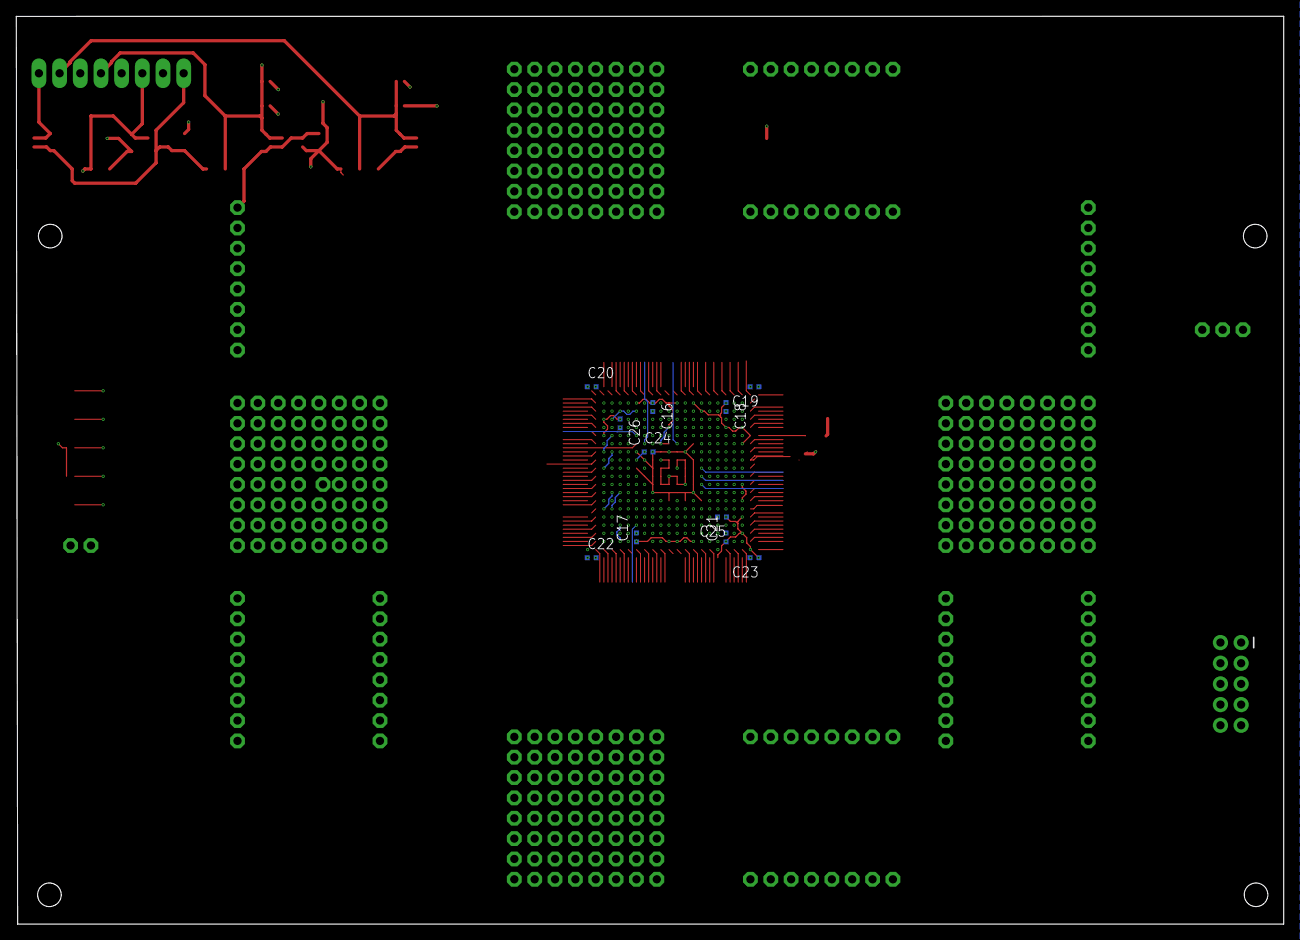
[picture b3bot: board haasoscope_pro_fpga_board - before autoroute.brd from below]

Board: 10 copper layers, 155.7 x 111.5 mm, 406 parts (11 on the bottom side), 358 nets.
